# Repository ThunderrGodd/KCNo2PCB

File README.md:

# KCNo2PCB
PCB for keycult No.2/65, open sourced

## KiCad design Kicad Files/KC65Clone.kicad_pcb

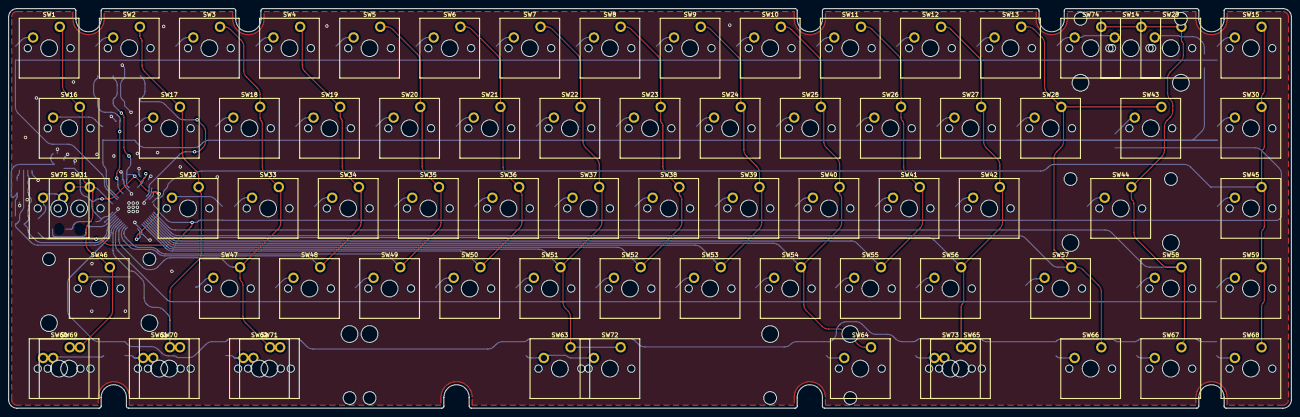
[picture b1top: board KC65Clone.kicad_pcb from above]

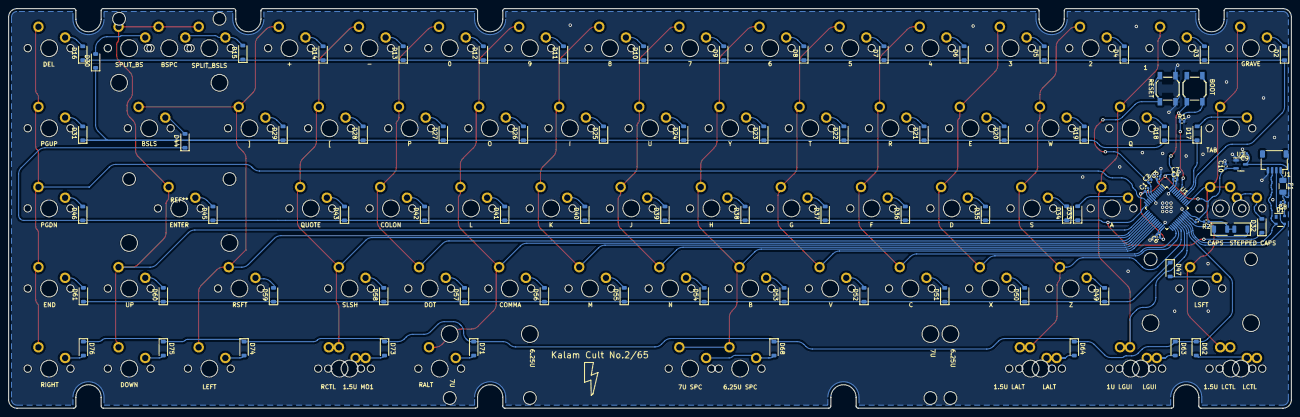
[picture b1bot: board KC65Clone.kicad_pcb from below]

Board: 2 copper layers, 305.0 x 95.0 mm, 164 parts (89 on the bottom side), 98 nets.

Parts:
BOOT: SKQGABE010; SW_SPST_SKQG_WithoutStem
C1, C2, C3, C4, C5, C6, C8: 100nF; C_0402_1005Metric
C7: 10nF; C_0402_1005Metric
C9, C10: 1uF; C_0402_1005Metric
D1: PRTR5V0U2X; SOT-143
D2, D3, D4, D5, D6, D7, D8, D9, D10, D11, D12, D13, D14, D15, D16, D17, D18, D19, D20, D21, D22, D23, D24, D25, D26, D27, D28, D29, D30, D31, D32, D33, D34, D35, D36, D37, D38, D39, D40, D41, D42, D43, D44, D45, D46, D47, D49, D50, D51, D52, D53, D54, D55, D56, D57, D58, D59, D60, D61, D62, D63, D64, D68, D71, D73, D74, D75, D76: D_Small_Filled; D_SOD-123
F1: Polyfuse; Fuse_1206_3216Metric
J1: Conn_01x04; JST_SH_SM04B-SRSS-TB_1x04-1MP_P1.00mm_Horizontal
LED1, LED2: LED; LED_1206_3216Metric_ReverseMount_Hole1.8x2.4mm
R1: 10k; R_0402_1005Metric
R2: 470R; R_0402_1005Metric
RESET: SKQGABE010; SW_SPST_SKQG_WithoutStem
SW1: GRAVE; SW_Cherry_MX_PCB_1.00u_valueprint
SW2: 1; SW_Cherry_MX_PCB_1.00u_valueprint
SW3: 2; SW_Cherry_MX_PCB_1.00u_valueprint
SW4: 3; SW_Cherry_MX_PCB_1.00u_valueprint
SW5: 4; SW_Cherry_MX_PCB_1.00u_valueprint
SW6: 5; SW_Cherry_MX_PCB_1.00u_valueprint
SW7: 6; SW_Cherry_MX_PCB_1.00u_valueprint
SW8: 7; SW_Cherry_MX_PCB_1.00u_valueprint
SW9: 8; SW_Cherry_MX_PCB_1.00u_valueprint
SW10: 9; SW_Cherry_MX_PCB_1.00u_valueprint
SW11: 0; SW_Cherry_MX_PCB_1.00u_valueprint
SW12: -; SW_Cherry_MX_PCB_1.00u_valueprint
SW13: +; SW_Cherry_MX_PCB_1.00u_valueprint
SW14: BSPC; SW_Cherry_MX_PCB_2.00u_valueprint
SW15: DEL; SW_Cherry_MX_PCB_1.00u_valueprint
SW16: TAB; SW_Cherry_MX_PCB_1.50u_valueprint
SW17: Q; SW_Cherry_MX_PCB_1.00u_valueprint
SW18: W; SW_Cherry_MX_PCB_1.00u_valueprint
SW19: E; SW_Cherry_MX_PCB_1.00u_valueprint
SW20: R; SW_Cherry_MX_PCB_1.00u_valueprint
SW21: T; SW_Cherry_MX_PCB_1.00u_valueprint
SW22: Y; SW_Cherry_MX_PCB_1.00u_valueprint
SW23: U; SW_Cherry_MX_PCB_1.00u_valueprint
SW24: I; SW_Cherry_MX_PCB_1.00u_valueprint
SW25: O; SW_Cherry_MX_PCB_1.00u_valueprint
SW26: P; SW_Cherry_MX_PCB_1.00u_valueprint
SW27: [; SW_Cherry_MX_PCB_1.00u_valueprint
SW28: ]; SW_Cherry_MX_PCB_1.00u_valueprint
SW29: SPLIT_BS; SW_Cherry_MX_PCB_1.00u_valueprint
SW30: PGUP; SW_Cherry_MX_PCB_1.00u_valueprint
SW31: CAPS; SW_Cherry_MX_PCB_1.75u_valueprint
SW32: A; SW_Cherry_MX_PCB_1.00u_valueprint
SW33: S; SW_Cherry_MX_PCB_1.00u_valueprint
SW34: D; SW_Cherry_MX_PCB_1.00u_valueprint
SW35: F; SW_Cherry_MX_PCB_1.00u_valueprint
SW36: G; SW_Cherry_MX_PCB_1.00u_valueprint
SW37: H; SW_Cherry_MX_PCB_1.00u_valueprint
SW38: J; SW_Cherry_MX_PCB_1.00u_valueprint
SW39: K; SW_Cherry_MX_PCB_1.00u_valueprint
SW40: L; SW_Cherry_MX_PCB_1.00u_valueprint
SW41: COLON; SW_Cherry_MX_PCB_1.00u_valueprint
SW42: QUOTE; SW_Cherry_MX_PCB_1.00u_valueprint
SW43: BSLS; SW_Cherry_MX_PCB_1.50u_valueprint
SW44: ENTER; SW_Cherry_MX_PCB_2.25u_valueprint
SW45: PGDN; SW_Cherry_MX_PCB_1.00u_valueprint
SW46: LSFT; SW_Cherry_MX_PCB_2.25u_valueprint
SW47: Z; SW_Cherry_MX_PCB_1.00u_valueprint
SW48: X; SW_Cherry_MX_PCB_1.00u_valueprint
SW49: C; SW_Cherry_MX_PCB_1.00u_valueprint
SW50: V; SW_Cherry_MX_PCB_1.00u_valueprint
SW51: B; SW_Cherry_MX_PCB_1.00u_valueprint
SW52: N; SW_Cherry_MX_PCB_1.00u_valueprint
SW53: M; SW_Cherry_MX_PCB_1.00u_valueprint
SW54: COMMA; SW_Cherry_MX_PCB_1.00u_valueprint
SW55: DOT; SW_Cherry_MX_PCB_1.00u_valueprint
SW56: SLSH; SW_Cherry_MX_PCB_1.00u_valueprint
SW57: RSFT; SW_Cherry_MX_PCB_1.75u_valueprint
SW58: UP; SW_Cherry_MX_PCB_1.00u_valueprint
SW59: END; SW_Cherry_MX_PCB_1.00u_valueprint
SW60: LCTL; SW_Cherry_MX_PCB_1.25u_valueprint
SW61: LGUI; SW_Cherry_MX_PCB_1.25u_valueprint
SW62: LALT; SW_Cherry_MX_PCB_1.25u_valueprint
SW63: 6.25U SPC; SW_Cherry_MX_PCB_6.25u
SW64: RALT; SW_Cherry_MX_PCB_1.25u_valueprint
SW65: RCTL; SW_Cherry_MX_PCB_1.25u_valueprint
SW66: LEFT; SW_Cherry_MX_PCB_1.00u_valueprint
SW67: DOWN; SW_Cherry_MX_PCB_1.00u_valueprint
SW68: RIGHT; SW_Cherry_MX_PCB_1.00u_valueprint
SW69: 1.5U LCTL; SW_Cherry_MX_PCB_1.50u_valueprint
SW70: 1U LGUI; SW_Cherry_MX_PCB_1.00u_valueprint
SW71: 1.5U LALT; SW_Cherry_MX_PCB_1.50u_valueprint
SW72: 7U SPC; SW_Cherry_MX_PCB_7.00u
SW73: 1.5U MO1; SW_Cherry_MX_PCB_1.50u_valueprint
SW74: SPLIT_BSLS; SW_Cherry_MX_PCB_1.00u_valueprint
SW75: STEPPED CAPS; SW_Cherry_MX_PCB_1.25u_valueprint
U1: STM32F072C8Tx; LQFP-48_7x7mm_P0.5mm
U2: XC6206P332MR; SOT-23-3

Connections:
+3.3V: BOOT.1, C1.1, C3.1, C4.1, C5.1, C6.1, C7.1, C10.1, R2.2, U1.1 (VBAT), U1.9 (VDDA), U1.24 (VDD), U1.36 (VDDIO2), U1.48 (VDD), U2.2 (VO)
+5V: C8.1, C9.1, D1.4 (VCC), F1.2, U2.3 (VI)
BOOT0: BOOT.2, R1.1, U1.44 (BOOT0)
CAPSLCK: LED1.1 (K), LED2.1 (K)
COL0: SW1.2, SW16.2, SW31.2, SW46.2, SW60.2, SW69.2, SW75.2, U1.37 (PA14)
COL1: SW2.2, SW17.2, SW32.2, SW61.2, SW70.2, U1.30 (PA9)
COL2: SW3.2, SW18.2, SW33.2, SW47.2, SW62.2, SW71.2, U1.28 (PB15)
COL3: SW4.2, SW19.2, SW34.2, SW48.2, U1.27 (PB14)
COL4: SW5.2, SW20.2, SW35.2, SW49.2, U1.26 (PB13)
COL5: SW6.2, SW21.2, SW36.2, SW50.2, U1.21 (PB10)
COL6: SW7.2, SW22.2, SW37.2, SW51.2, SW63.2, SW72.2, U1.20 (PB2)
COL7: SW8.2, SW23.2, SW38.2, SW52.2, U1.19 (PB1)
COL8: SW9.2, SW24.2, SW39.2, SW53.2, U1.18 (PB0)
COL9: SW10.2, SW25.2, SW40.2, SW54.2, SW64.2, U1.17 (PA7)
COL10: SW11.2, SW26.2, SW41.2, SW55.2, U1.16 (PA6)
COL11: SW12.2, SW27.2, SW42.2, SW56.2, SW65.2, SW73.2, U1.15 (PA5)
COL12: SW13.2, SW28.2, SW43.2, SW57.2, SW66.2, U1.14 (PA4)
COL13: SW14.2, SW29.2, SW44.2, SW58.2, SW67.2, SW74.2, U1.13 (PA3)
COL14: SW15.2, SW30.2, SW45.2, SW59.2, SW68.2, U1.11 (PA1)
D+: D1.2 (I/O1), J1.3, U1.33 (PA12)
D-: D1.3 (I/O2), J1.2, U1.32 (PA11)
GND: C1.2, C2.2, C3.2, C4.2, C5.2, C6.2, C7.2, C8.2, C9.2, C10.2, J1.4, R1.2, RESET.2, U1.8 (VSSA), U1.23 (VSS), U1.35 (VSS), U1.47 (VSS), U2.1 (GND)
NRST: C2.1, RESET.1, U1.7 (NRST)
unnamed: D2.2 (A), SW1.1
unnamed: D3.2 (A), SW2.1
unnamed: D4.2 (A), SW3.1
unnamed: D5.2 (A), SW4.1
unnamed: D6.2 (A), SW5.1
unnamed: D7.2 (A), SW6.1
unnamed: D8.2 (A), SW7.1
unnamed: D9.2 (A), SW8.1
unnamed: D10.2 (A), SW9.1
unnamed: D11.2 (A), SW10.1
unnamed: D12.2 (A), SW11.1
unnamed: D13.2 (A), SW12.1
unnamed: D14.2 (A), SW13.1
unnamed: D15.2 (A), SW14.1, SW74.1
unnamed: D16.2 (A), SW15.1
unnamed: D17.2 (A), SW16.1
unnamed: D18.2 (A), SW17.1
unnamed: D19.2 (A), SW18.1
unnamed: D20.2 (A), SW19.1
unnamed: D21.2 (A), SW20.1
unnamed: D22.2 (A), SW21.1
unnamed: D23.2 (A), SW22.1
unnamed: D24.2 (A), SW23.1
unnamed: D25.2 (A), SW24.1
unnamed: D26.2 (A), SW25.1
unnamed: D27.2 (A), SW26.1
unnamed: D28.2 (A), SW27.1
unnamed: D29.2 (A), SW28.1
unnamed: D30.2 (A), SW29.1
unnamed: D31.2 (A), SW30.1
unnamed: D32.2 (A), SW31.1, SW75.1
unnamed: D33.2 (A), SW32.1
unnamed: D34.2 (A), SW33.1
unnamed: D35.2 (A), SW34.1
unnamed: D36.2 (A), SW35.1
unnamed: D37.2 (A), SW36.1
unnamed: D38.2 (A), SW37.1
unnamed: D39.2 (A), SW38.1
unnamed: D40.2 (A), SW39.1
unnamed: D41.2 (A), SW40.1
unnamed: D42.2 (A), SW41.1
unnamed: D43.2 (A), SW42.1
unnamed: D44.2 (A), SW43.1
unnamed: D45.2 (A), SW44.1
unnamed: D46.2 (A), SW45.1
unnamed: D47.2 (A), SW46.1
unnamed: D49.2 (A), SW47.1
unnamed: D50.2 (A), SW48.1
unnamed: D51.2 (A), SW49.1
unnamed: D52.2 (A), SW50.1
unnamed: D53.2 (A), SW51.1
unnamed: D54.2 (A), SW52.1
unnamed: D55.2 (A), SW53.1
unnamed: D56.2 (A), SW54.1
unnamed: D57.2 (A), SW55.1
unnamed: D58.2 (A), SW56.1
unnamed: D59.2 (A), SW57.1
unnamed: D60.2 (A), SW58.1
unnamed: D61.2 (A), SW59.1
unnamed: D62.2 (A), SW60.1, SW69.1
unnamed: D63.2 (A), SW61.1, SW70.1
unnamed: D64.2 (A), SW62.1, SW71.1
unnamed: D68.2 (A), SW63.1, SW72.1
unnamed: D71.2 (A), SW64.1
unnamed: D73.2 (A), SW65.1, SW73.1
unnamed: D74.2 (A), SW66.1
unnamed: D75.2 (A), SW67.1
unnamed: D76.2 (A), SW68.1
unnamed: LED1.2 (A), LED2.2 (A), R2.1
ROW0: D2.1 (K), D3.1 (K), D4.1 (K), D5.1 (K), D6.1 (K), D7.1 (K), D8.1 (K), D9.1 (K), D10.1 (K), D11.1 (K), D12.1 (K), D13.1 (K), D14.1 (K), D15.1 (K), D16.1 (K), U1.40 (PB4)
ROW1: D17.1 (K), D18.1 (K), D19.1 (K), D20.1 (K), D21.1 (K), D22.1 (K), D23.1 (K), D24.1 (K), D25.1 (K), D26.1 (K), D27.1 (K), D28.1 (K), D29.1 (K), D30.1 (K), D31.1 (K), U1.41 (PB5)
ROW2: D32.1 (K), D33.1 (K), D34.1 (K), D35.1 (K), D36.1 (K), D37.1 (K), D38.1 (K), D39.1 (K), D40.1 (K), D41.1 (K), D42.1 (K), D43.1 (K), D44.1 (K), D45.1 (K), D46.1 (K), U1.12 (PA2)
ROW3: D47.1 (K), D49.1 (K), D50.1 (K), D51.1 (K), D52.1 (K), D53.1 (K), D54.1 (K), D55.1 (K), D56.1 (K), D57.1 (K), D58.1 (K), D59.1 (K), D60.1 (K), D61.1 (K), U1.29 (PA8)
ROW4: D62.1 (K), D63.1 (K), D64.1 (K), D68.1 (K), D71.1 (K), D73.1 (K), D74.1 (K), D75.1 (K), D76.1 (K), U1.31 (PA10)
VBUS: F1.1, J1.1

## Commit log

2024-09-01 Upload Kicad Files
